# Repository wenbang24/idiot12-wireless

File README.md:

# idiot12-wireless
the idiot12, now in wireless form factor (see [https://github.com/wenbang24/idiot17](https://github.com/wenbang24/idiot17) and [https://github.com/wenbang24/idiot12](https://github.com/wenbang24/idiot12) for context)

a wireless split keyboard with every alpha key fitting on one layer with 12 keys
uses holyiot 18010 nRF52840 module, USB-C charging, and Kailh Choc switches

reduce your finger movement, and have your thumb and pinky free to do other things

# BOM
This is just for one side; double it for both sides.
|Designator                  |Footprint                                       |Quantity|Value                      |LCSC Part #|
|----------------------------|------------------------------------------------|--------|---------------------------|-----------|
|C2                          |0603                                            |1       |4u7                        |C19666     |
|C3, C4                      |0603                                            |2       |10u                        |C19702     |
|C5, C6                      |0603                                            |2       |1u                         |C15849     |
|C7                          |0603                                            |1       |100n                       |C14663     |
|D2                          |0603                                            |1       |LED_Small                  |C2286      |
|F1                          |1206                                            |1       |Fuse_Small                 |C151162    |
|FB2                         |0402                                            |1       |FerriteBead_Small          |C160976    |
|J1                          |USB_C_Receptacle_HRO_TYPE-C-31-M-12             |1       |USB_C_Receptacle_USB2.0_16P|C165948    |
|J3                          |JST_PH_S2B-PH-SM4-TB_1x02-1MP_P2.00mm_Horizontal|1       |Conn_01x02_MountingPin     |C295747    |
|J4                          |PinHeader_2x03_P2.54mm_Vertical                 |1       |Conn_02x03_Odd_Even        |C5116479   |
|R1, R2                      |0603                                            |2       |5k1                        |C23186     |
|R3                          |0603                                            |1       |1k5                        |C22843     |
|R4                          |0603                                            |1       |5k                         |C23186     |
|R5                          |0603                                            |1       |806k                       |C403362    |
|R6                          |0603                                            |1       |2M                         |C4077045   |
|SW1                         |SW_SPDT_PCM12                                   |1       |SW_SPDT                    |C221841    |
|SW2                         |TS-1088R-02526                                  |1       |RST                        |C720477    |
|SW3, SW4, SW5, SW6, SW7, SW8|SW_choc_v1_HS_CPG135001S30_1u                   |6       |Kailh_Choc                 |           |
|U1                          |nRF52840_holyiot_18010                          |1       |nRF52840_holyiot_18010     |           |
|U2                          |SOT-23-6                                        |1       |SRV05-4                    |C316033    |
|U3                          |SOP-8-1EP_4.57x4.57mm_P1.27mm_EP4.57x4.45mm     |1       |TP4056                     |C16581     |
|U4                          |SOT-23-3                                        |1       |XC6206PxxxMR               |C5446      |

## Parts to source yourself:
- Holyiot 18010 e.g. [this](https://www.aliexpress.com/item/32868002366.html?spm=a2g0o.productlist.main.2.74edNdM5NdM5Lu&algo_pvid=63543511-576a-4598-869e-381ab8d96dd6&algo_exp_id=63543511-576a-4598-869e-381ab8d96dd6-1&pdp_ext_f=%7B%22order%22%3A%228%22%2C%22eval%22%3A%221%22%7D&pdp_npi=4%40dis%21AUD%2110.59%2110.59%21%21%216.77%216.77%21%402103273e17500347440062660e8dd6%2112000030046383139%21sea%21AU%212685707787%21ACX&curPageLogUid=FLPTO15Lm8sv&utparam-url=scene%3Asearch%7Cquery_from%3A)
- USB-C receptacle (TYPE-C-31-M-12) e.g. [this](https://www.aliexpress.com/item/1005003285152827.html)
- SRV-05 e.g. [this](https://www.aliexpress.com/item/1005007499115687.html?spm=a2g0o.productlist.main.1.370c2eabRIuU4c&algo_pvid=3902107f-d815-4f71-892f-0f4ff5babd23&algo_exp_id=3902107f-d815-4f71-892f-0f4ff5babd23-0&pdp_ext_f=%7B%22order%22%3A%2263%22%2C%22eval%22%3A%221%22%7D&pdp_npi=4%40dis%21AUD%213.00%211.55%21%21%211.92%210.99%21%402101e7f617500346809515112e5430%2112000041034899345%21sea%21AU%212685707787%21ACX&curPageLogUid=wGPht6PxB6Zn&utparam-url=scene%3Asearch%7Cquery_from%3A)
- 2.54mm 2x3 pin header e.g. [this](https://www.aliexpress.com/item/4000303366348.html?spm=a2g0o.productlist.main.9.b9d0670dk3BV5M&algo_pvid=57cdfcc2-917a-4bc1-85a6-6d20830b449f&algo_exp_id=57cdfcc2-917a-4bc1-85a6-6d20830b449f-8&pdp_ext_f=%7B%22order%22%3A%2212%22%2C%22eval%22%3A%221%22%7D&pdp_npi=4%40dis%21AUD%211.91%211.55%21%21%211.22%210.99%21%402101eac917500339708216026e6416%2112000044746020817%21sea%21AU%212685707787%21ACX&curPageLogUid=530t4aMtfrUG&utparam-url=scene%3Asearch%7Cquery_from%3A)
- 3.7V LiPo battery (around 120mAh) with 2mm JST PH header e.g. [this](https://core-electronics.com.au/lipo-polymer-lithium-ion-battery-120mah.html)
- 4x M3 10mm screws e.g. [this](https://www.bunnings.com.au/pinnacle-m3-x-10mm-zinc-plated-round-head-bolts-and-nuts-20-pack_p0247262)
- 6x Kailh Choc switches e.g. [this](https://www.aliexpress.com/item/1005005883472162.html?spm=a2g0o.productlist.main.9.4860194bsF2axc&algo_pvid=96efd269-fd40-4912-bcc3-c3c9bf343ace&algo_exp_id=96efd269-fd40-4912-bcc3-c3c9bf343ace-8&pdp_ext_f=%7B%22order%22%3A%22513%22%2C%22eval%22%3A%221%22%7D&pdp_npi=4%40dis%21AUD%2129.31%2121.49%21%21%2118.73%2113.73%21%402101ea8c17500345939608243e6881%2112000034695877956%21sea%21AU%212685707787%21ACX&curPageLogUid=j4LjWbErE5Ol&utparam-url=scene%3Asearch%7Cquery_from%3A)
- 6x Kailh Choc keycaps e.g. [this](https://www.aliexpress.com/item/32949747794.html?spm=a2g0o.productlist.main.1.460d5999529yoW&algo_pvid=ede377b0-6f3c-4e11-a73a-7adab6daf68c&algo_exp_id=ede377b0-6f3c-4e11-a73a-7adab6daf68c-0&pdp_ext_f=%7B%22order%22%3A%224%22%2C%22eval%22%3A%221%22%7D&pdp_npi=4%40dis%21AUD%210.31%210.31%21%21%210.20%210.20%21%40210308a417500347822807759e1e9a%2166232934108%21sea%21AU%212685707787%21ACX&curPageLogUid=KRoYxvyJp5yq&utparam-url=scene%3Asearch%7Cquery_from%3A)

PCBA cost: $34.56
**Cost**: $84.29 USD (excluding shipping)

Estimated total: $100 USD

(prices converted from AUD to USD, accurate as of 2025-06-16)

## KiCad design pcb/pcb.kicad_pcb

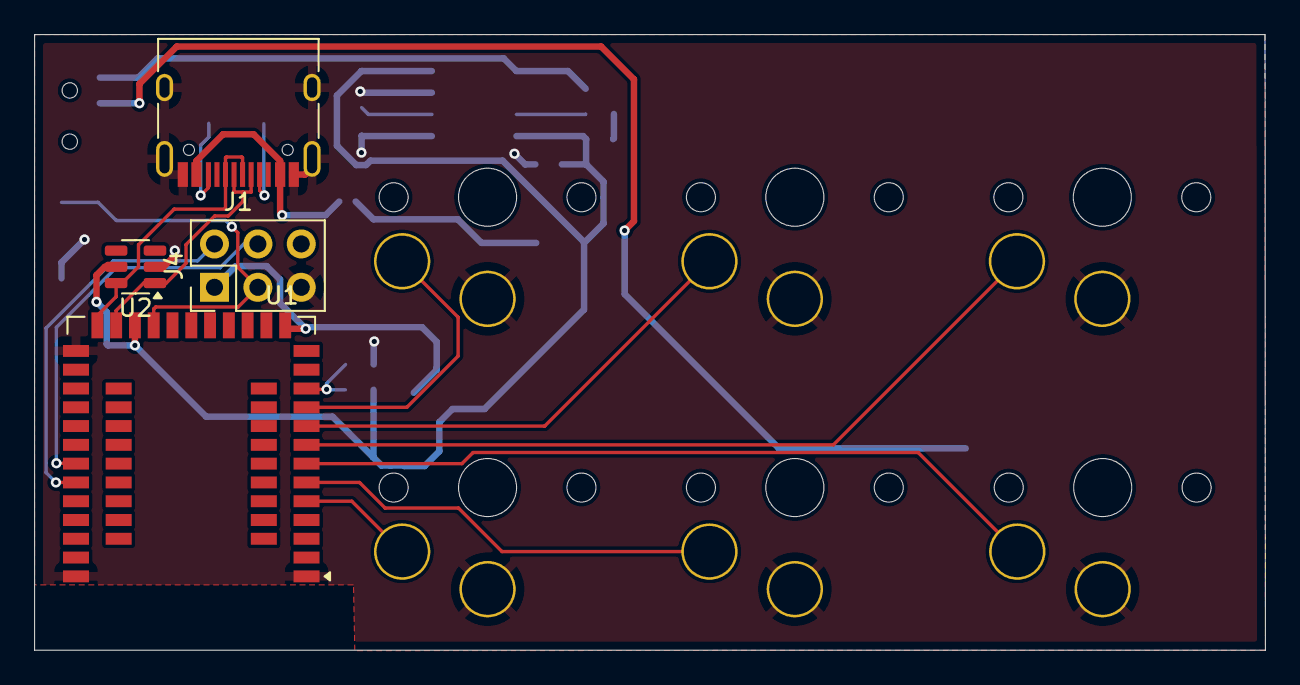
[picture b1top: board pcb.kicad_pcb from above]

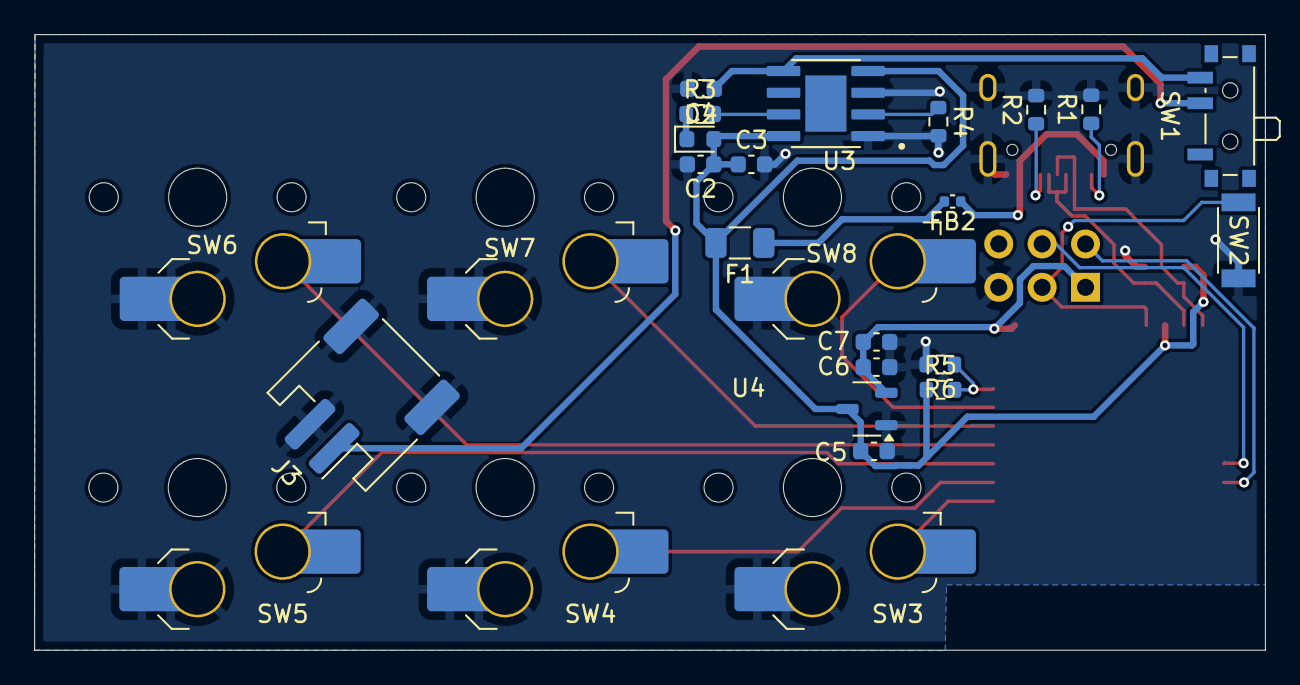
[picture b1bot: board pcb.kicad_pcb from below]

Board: 2 copper layers, 72.1 x 36.1 mm, 30 parts (26 on the bottom side), 24 nets.

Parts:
C2: 4u7; C_0603_1608Metric
C3, C4: 10u; C_0603_1608Metric
C5, C6: 1u; C_0603_1608Metric
C7: 100n; C_0603_1608Metric
D2: LED_Small; LED_0603_1608Metric
F1: Fuse_Small; Fuse_1206_3216Metric
FB2: FerriteBead_Small; C_0402_1005Metric
J1: USB_C_Receptacle_USB2.0_16P; USB_C_Receptacle_HRO_TYPE-C-31-M-12
J3: Conn_01x02_MountingPin; JST_PH_S2B-PH-SM4-TB_1x02-1MP_P2.00mm_Horizontal
J4: Conn_02x03_Odd_Even; PinHeader_2x03_P2.54mm_Vertical
R1, R2: 5k1; R_0603_1608Metric
R3: 1k5; R_0603_1608Metric
R4: 5k; R_0603_1608Metric
R5: 806k; R_0603_1608Metric
R6: 2M; R_0603_1608Metric
SW1: SW_SPDT; SW_SPDT_PCM12
SW2: RST; TS-1088R-02526
SW3, SW4, SW5, SW6, SW7, SW8: Kailh_Choc; SW_choc_v1_HS_CPG135001S30_1u
U1: nRF52840_holyiot_18010
U2: SRV05-4; SOT-23-6
U3: TP4056; SOP127P600X175-9N
U4: XC6206PxxxMR; SOT-23-3

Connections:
+3.3V: C6.1, C7.1, J4.1, U1.14 (VDD_nRF), U4.2 (VO)
+5V: C2.1, C3.1, C5.1, D2.2 (A), F1.2, R5.1, U1.22 (VBUS), U2.5 (VP), U3.4 (VCC), U3.8 (CE), U4.3 (VI)
+BATT: C4.1, SW1.3 (C), U3.5 (BAT)
/RST: J4.3, SW2.1, U1.21 (P0.18-RESET)
/SWDCLK: J4.4, U1.31 (SWDCLK)
/SWDIO: J4.2, U1.32 (SWDIO)
/USB-D+: J1.A6 (D+), J1.B6 (D+), U1.24 (D+), U2.6 (IO4)
/USB-D-: J1.A7 (D-), J1.B7 (D-), U1.23 (D-), U2.1 (IO1)
/VSENSE: R5.2, R6.1, U1.11 (P0.31-LF-A)
/sw3: SW3.1, U1.5 (P1.15-LF)
/sw4: SW4.1, U1.6 (P0.03-LF-A)
/sw5: SW5.1, U1.7 (P0.02-LF-A)
/sw6: SW6.1, U1.8 (P0.28-LF-A)
/sw7: SW7.1, U1.9 (P0.29-LF-A)
/sw8: SW8.1, U1.10 (P0.30-LF-A)
GND: C2.2, C3.2, C4.2, C5.2, C6.2, C7.2, J1.A1 (GND), J1.A12 (GND), J1.B1 (GND), J1.B12 (GND), J1.S1 (SHIELD), J3.2, J3.MP (MountPin), J4.5, R1.2, R2.2, R4.2, R6.2, SW2.2, SW3.2, SW4.2, SW5.2, SW6.2, SW7.2, SW8.2, U1.1 (GND), U1.25 (GND), U1.37 (GND), U2.2 (VN), U3.1 (TEMP), U3.3 (GND), U4.1 (GND)
unnamed: D2.1 (K), R3.1
unnamed: F1.1, FB2.2
unnamed: J1.A5 (CC1), R2.1
unnamed: J1.B5 (CC2), R1.1
unnamed: J3.1, SW1.2 (B)
unnamed: R3.2, U3.7 (CHRG)
unnamed: R4.1, U3.2 (PROG)
VBUS: FB2.1, J1.A4 (VBUS), J1.A9 (VBUS), J1.B4 (VBUS), J1.B9 (VBUS)

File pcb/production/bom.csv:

Designator,Footprint,Quantity,Value,LCSC Part #
C2,0603,1,4u7,C19666
"C3, C4",0603,2,10u,C19702
"C5, C6",0603,2,1u,C15849
C7,0603,1,100n,C14663
D2,0603,1,LED_Small,C2286
F1,1206,1,Fuse_Small,C151162
FB2,0402,1,FerriteBead_Small,C160976
J3,JST_PH_S2B-PH-SM4-TB_1x02-1MP_P2.00mm_Horizontal,1,Conn_01x02_MountingPin,C295747
"R1, R2",0603,2,5k1,C23186
R3,0603,1,1k5,C22843
R4,0603,1,5k,C23186
R5,0603,1,806k,C403362
R6,0603,1,2M,C4077045
SW1,SW_SPDT_PCM12,1,SW_SPDT,C221841
SW2,TS-1088R-02526,1,RST,C720477
"SW3, SW4, SW5, SW6, SW7, SW8",SW_choc_v1_HS_CPG135001S30_1u,6,Kailh_Choc,
U3,SOP127P600X175-9N,1,TP4056,C16581
U4,SOT-23-3,1,XC6206PxxxMR,C5446

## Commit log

2025-05-22 add initial keymap
2025-05-23 add submodules
2025-05-23 basic usb schematics
2025-05-24 schematic 1st draft
2025-05-24 remove unecessary battery voltage sensing circuitry
2025-05-24 journal
2025-05-25 finish footprint assignment
2025-05-26 routing is hard
2025-05-29 finish routing first draft
2025-05-29 pcb routing
2025-05-30 one one gnd net, also get rid of some components
2025-05-30 continue routing
2025-05-30 backups?
2025-05-30 finish routing 2nd draft
2025-05-31 forgot to add images to journal
2025-06-03 update ground and 5v pours to cover the whole board
2025-06-09 update gnd pour
2025-06-13 pcb v3 - 2 layers again
2025-06-15 silkscreen
2025-06-15 backup
2025-06-15 small changes to pcb, also did some bom
2025-06-16 case
2025-06-16 images
2025-06-16 not really sure
2025-06-16 bom and gerbers
2025-06-16 a few more images
2025-06-16 finish readme
2025-06-16 formatting error in readme
2025-06-16 total time
2025-06-19 firmware in zmk (wow that was hard)
2025-06-19 journal firmware
2025-06-20 update prod files
2025-06-20 new price estimates
2025-06-22 update tp4056 footprint
2025-06-23 small changes to bom
2025-07-08 assembly 1
2025-07-15 aaaaaaaaaa
